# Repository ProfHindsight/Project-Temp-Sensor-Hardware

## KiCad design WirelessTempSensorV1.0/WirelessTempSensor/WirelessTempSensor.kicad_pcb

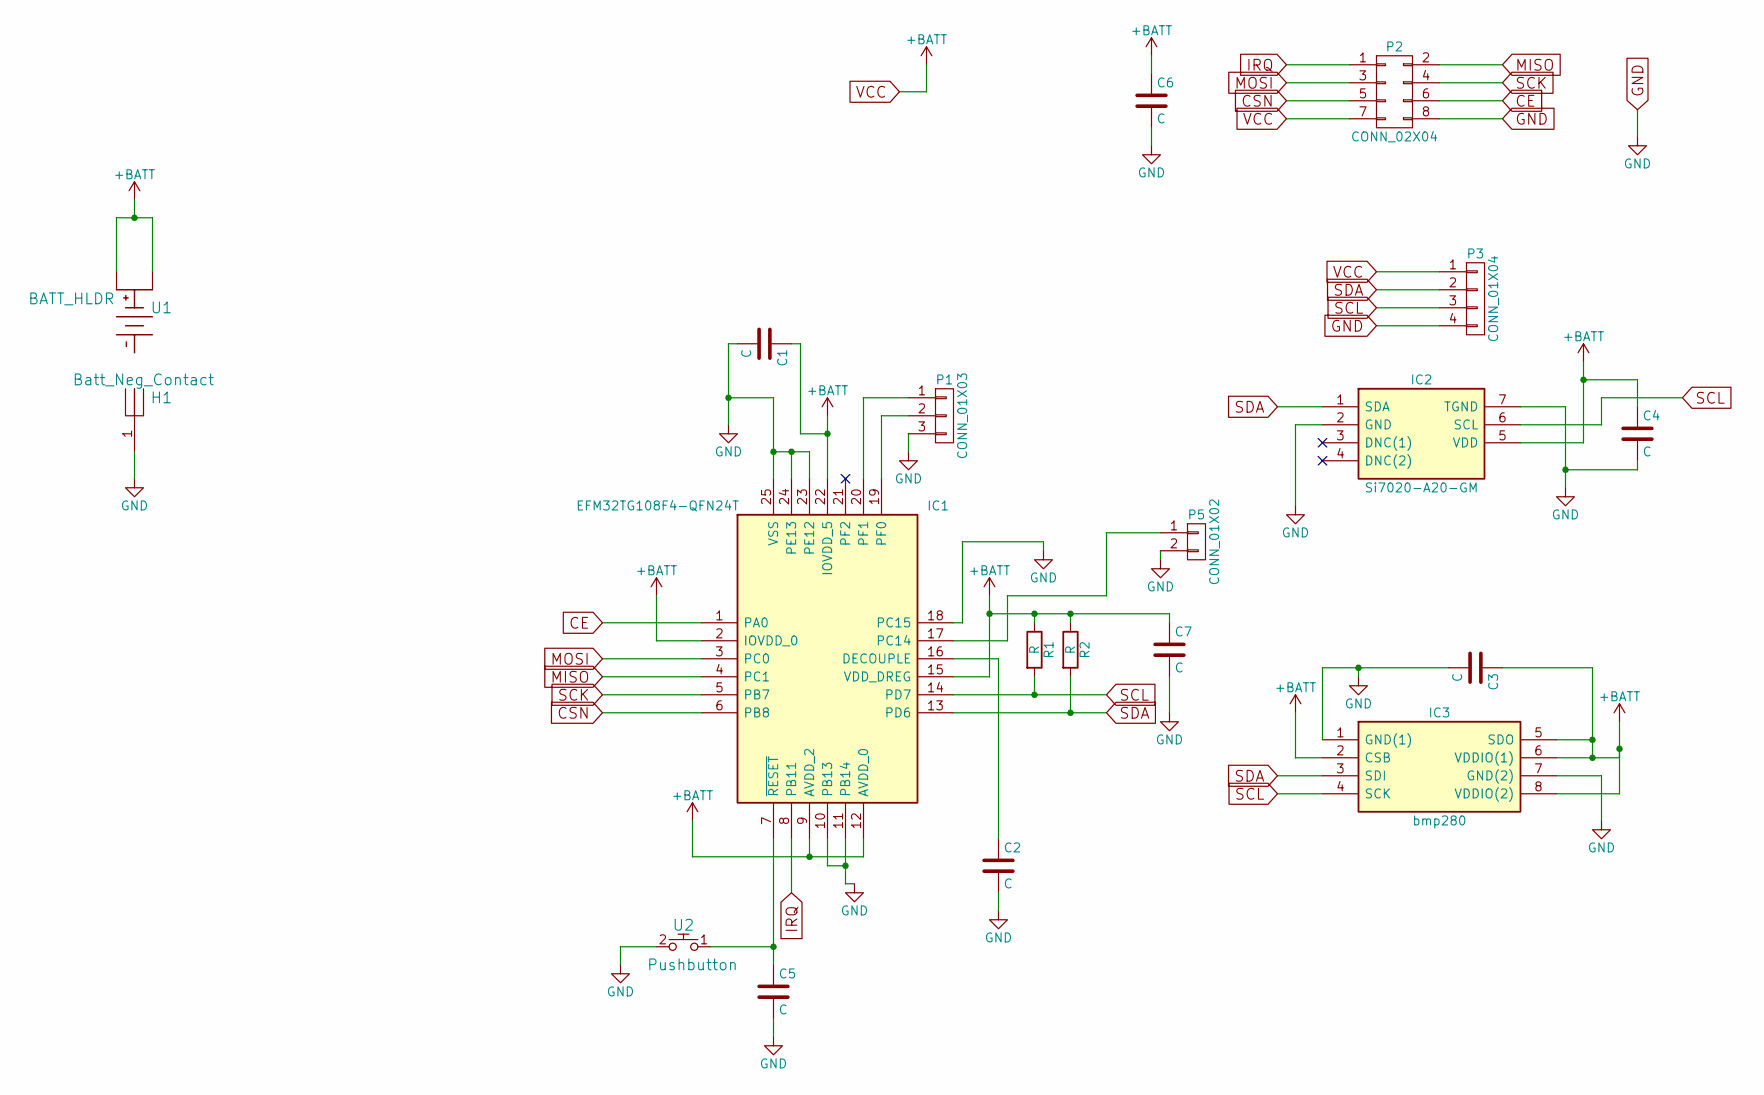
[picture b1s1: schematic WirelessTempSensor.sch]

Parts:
C1, C2, C3, C4, C5, C6, C7: C; C_0402
H1: Batt_Neg_Contact
IC1: EFM32TG108F4-QFN24T; QFN65P500X500X90-25N; Manufacturer_Part_Number EFM32TG108F4-QFN24T
IC2: Si7020-A20-GM; SON100P300X300X80-7N; Manufacturer_Part_Number Si7020-A20-GM
IC3: bmp280; 8-PIN-METAL-LID-LGA; Manufacturer_Part_Number bmp280
P1: CONN_01X03; Conn_1x3_SMD
P2: CONN_02X04; SDL-108-X-XX_2x04
P3: CONN_01X04; Conn_1x4_SMD
P5: CONN_01X02; Conn_1x2_SMD
R1, R2: R; R_0402
U1: BATT_HLDR; BAT-HLD-001
U2: Pushbutton; PB-P010336

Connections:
CE: IC1.1 (PA0), P2.6
CSN: IC1.6 (PB8), P2.5
GND: C1.2, C2.2, C3.2, C4.2, C5.2, C6.2, C7.2, H1.1, IC1.10 (PB13), IC1.11 (PB14), IC1.18 (PC15), IC1.23 (PE12), IC1.24 (PE13), IC1.25 (VSS), IC2.2 (GND), IC2.7 (TGND), IC3.1 (GND(1)), IC3.7 (GND(2)), P1.3, P2.8, P3.4, P5.2, U2.2
IRQ: IC1.8 (PB11), P2.1
MISO: IC1.4 (PC1), P2.2
MOSI: IC1.3 (PC0), P2.3
unnamed: C2.1, IC1.16 (DECOUPLE)
unnamed: C5.1, IC1.7 (~RESET), U2.1
unnamed: IC1.17 (PC14), P5.1
unnamed: IC1.19 (PF0), P1.2
unnamed: IC1.20 (PF1), P1.1
SCK: IC1.5 (PB7), P2.4
SCL: IC1.14 (PD7), IC2.6 (SCL), IC3.4 (SCK), P3.3, R1.2
SDA: IC1.13 (PD6), IC2.1 (SDA), IC3.3 (SDI), P3.2, R2.2
VCC: C1.1, C3.1, C4.1, C6.1, C7.1, IC1.2 (IOVDD_0), IC1.9 (AVDD_2), IC1.12 (AVDD_0), IC1.15 (VDD_DREG), IC1.22 (IOVDD_5), IC2.5 (VDD), IC3.2 (CSB), IC3.5 (SDO), IC3.6 (VDDIO(1)), IC3.8 (VDDIO(2)), P2.7, P3.1, R1.1, R2.1, U1.1, U1.3

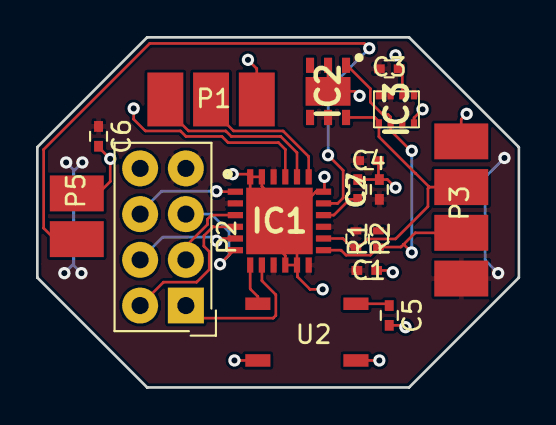
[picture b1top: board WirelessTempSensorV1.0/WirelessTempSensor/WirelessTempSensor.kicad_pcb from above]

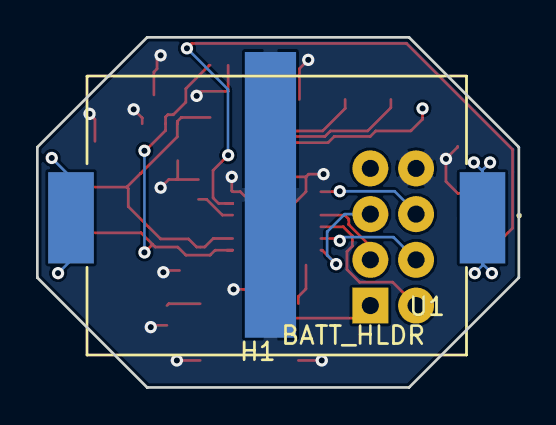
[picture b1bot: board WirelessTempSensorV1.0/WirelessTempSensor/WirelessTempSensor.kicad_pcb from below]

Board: 2 copper layers, 26.8 x 19.5 mm, 19 parts (2 on the bottom side), 15 nets.

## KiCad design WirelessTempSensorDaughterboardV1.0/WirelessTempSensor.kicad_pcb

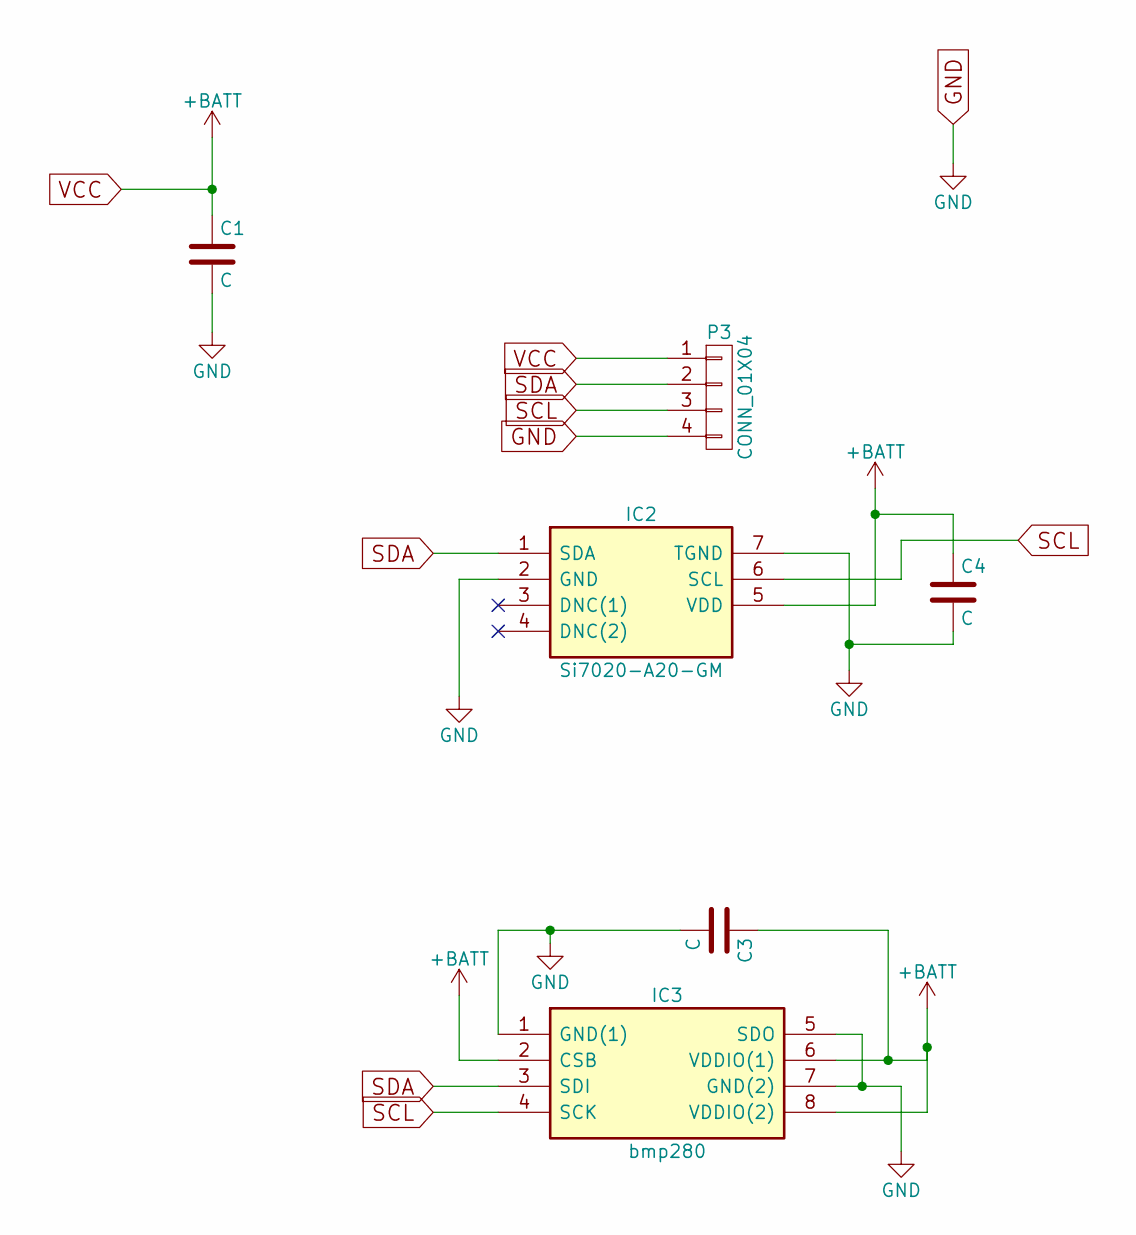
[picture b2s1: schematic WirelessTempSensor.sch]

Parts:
C1, C3, C4: C; C_0402
IC2: Si7020-A20-GM; SON100P300X300X80-7N; Manufacturer_Part_Number Si7020-A20-GM
IC3: bmp280; 8-PIN-METAL-LID-LGA; Manufacturer_Part_Number bmp280
P3: CONN_01X04; Conn_1x4_SMD

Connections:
GND: C1.2, C3.2, C4.2, IC2.2 (GND), IC2.7 (TGND), IC3.1 (GND(1)), IC3.5 (SDO), IC3.7 (GND(2)), P3.4
SCL: IC2.6 (SCL), IC3.4 (SCK), P3.3
SDA: IC2.1 (SDA), IC3.3 (SDI), P3.2
VCC: C1.1, C3.1, C4.1, IC2.5 (VDD), IC3.2 (CSB), IC3.6 (VDDIO(1)), IC3.8 (VDDIO(2)), P3.1

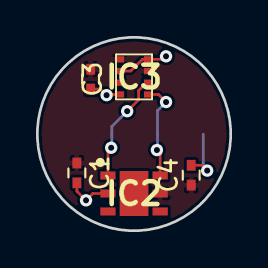
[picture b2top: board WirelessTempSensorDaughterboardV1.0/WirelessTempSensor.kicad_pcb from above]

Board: 2 copper layers, 10.7 x 10.7 mm, 6 parts (1 on the bottom side), 4 nets.

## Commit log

2018-09-09 :octocat: Added .gitattributes & .gitignore files
2018-09-09 Adding initial files
2018-09-09 Remembering to include the project properties in the instructions
2018-09-10 Adding RPi folder structure
2018-10-02 Generating binaries

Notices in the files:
parts and their libraries:
Copyright 2016 Accelerated Designs. All rights reserved.
